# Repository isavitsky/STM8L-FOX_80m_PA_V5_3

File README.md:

# STM8L-FOX_80m_PA_V5_3
STM8L 80m fox power amplifier board schematics and PCB version 5.3

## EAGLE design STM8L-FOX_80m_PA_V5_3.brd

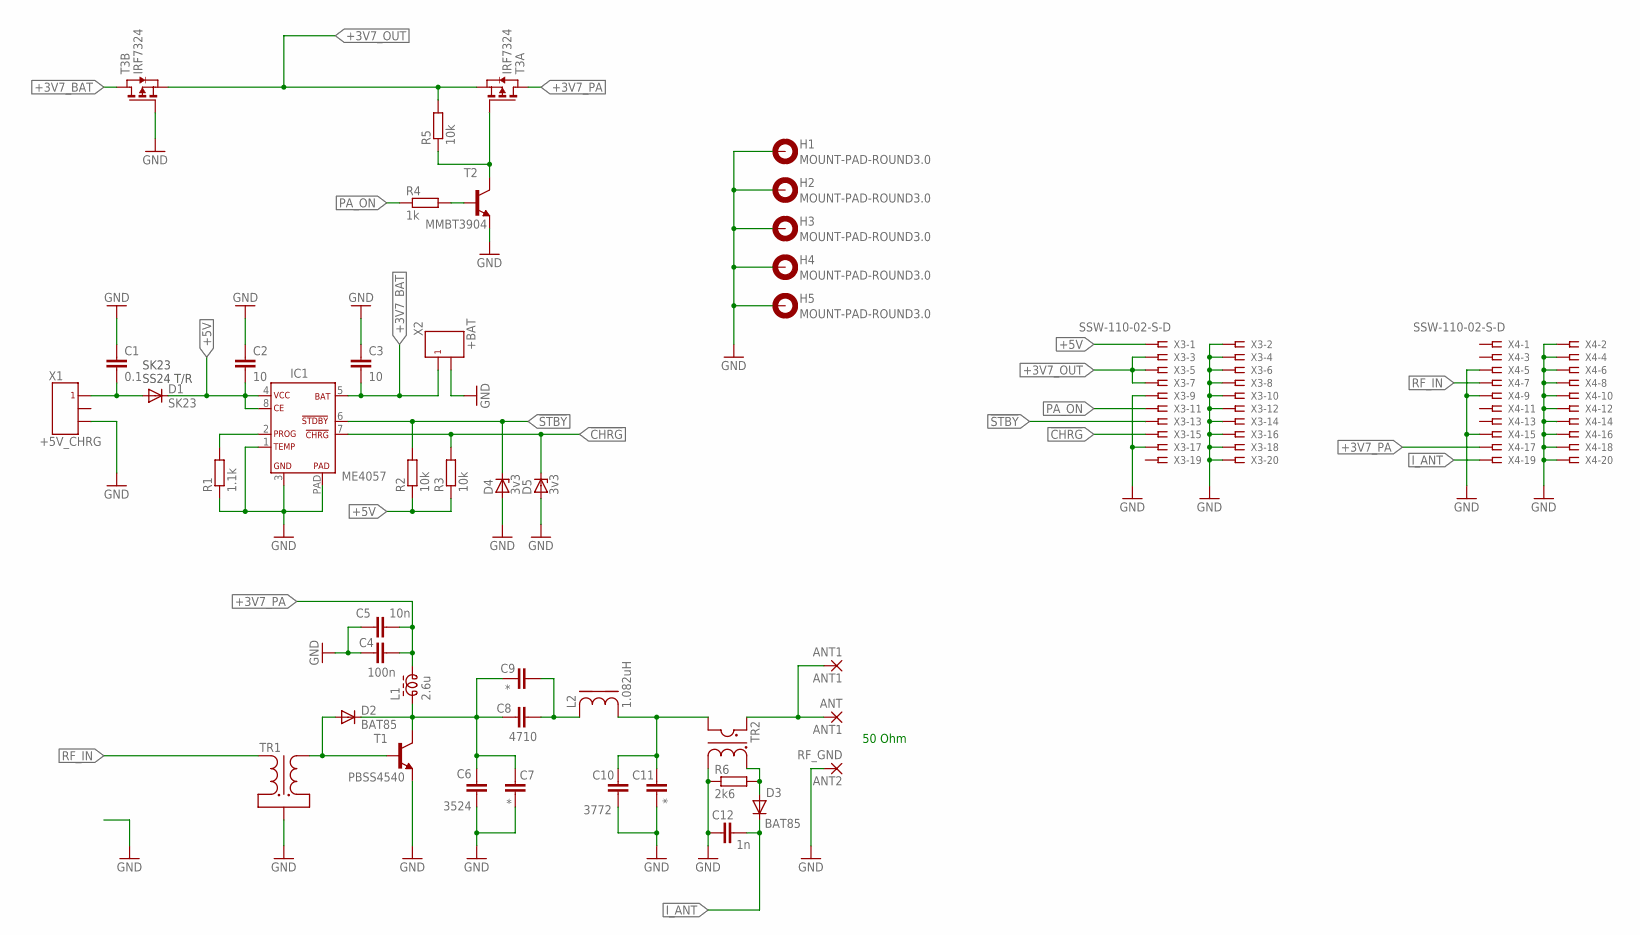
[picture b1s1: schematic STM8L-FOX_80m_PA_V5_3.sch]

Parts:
ANT, ANT1: ANT1; 2,54/0,8
C1: 0.1; C1206K
C2, C3: 10; C1206K
C4: 100n; C1206K
C5: 10n; C1206K
C6: 3524; C1206K
C7, C9, C11: *; C1206K
C8: 4710; C1206K
C10: 3772; C1206K
C12: 1n; C1206K
D1: SK23; DO-214AC
D2, D3: BAT85; DO34-7
D4, D5: 3v3; SOT23
H1, H2, H3, H4, H5: MOUNT-PAD-ROUND3.0; 3,0-PAD
IC1: ME4057A; SOP08-PP
L1: 2.6u; ZD6-3W
L2: 1.082uH; T68_COIL
R1: 1.1k; R1206
R2, R3, R5: 10k; R1206
R4: 1k; R1206
R6: 2k6; R1206
RF_GND: ANT2; 2,54/0,8
T1: PBSS4540; SOT223
T2: MMBT3904; SOT23-BEC
T3: IRF7324; SO8
TR1: K7X4X2_TRANS_1V1
TR2: K7X4X2_TRANS_CURRENT
X1: +5V_CHRG; A2501WR-3P
X2: +BAT; A2501WR-2P
X3, X4: SSW-110-02-S-D

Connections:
!CHRG!: D5.3 (C), IC1.7, R3.2, X3.15
!STBY!: D4.3 (C), IC1.6, R2.2, X3.13
+3V7_BAT: C3.2, IC1.5, T3.5 (D), T3.6 (D), X2.P$1
+3V7_OUT: R5.2, T3.1 (S), T3.3 (S), X3.3, X3.5, X3.7
+3V7_PA: C4.2, C5.1, L1.2, T3.7 (D), T3.8 (D), X4.17
+5V: C2.2, D1.C, IC1.4, IC1.8, R2.1, R3.1, X3.1
CHRGR: C1.2, D1.A, X1.P$1
GND: C1.1, C2.1, C3.1, C4.1, C5.2, C6.2, C7.2, C10.2, C11.2, C12.1, D4.1 (A), D5.1 (A), H1.B3,0, H2.B3,0, H3.B3,0, H4.B3,0, H5.B3,0, IC1.1, IC1.3, IC1.PAD, R1.1, R6.1, RF_GND.1, T1.3 (E), T2.E, T3.4 (G), TR1.P$1, TR2.P$4, X1.P$3, X2.P$2, X3.2, X3.4, X3.6, X3.8, X3.9, X3.10, X3.12, X3.14, X3.16, X3.17, X3.18, X3.20, X4.2, X4.4, X4.5, X4.6, X4.8, X4.9, X4.10, X4.12, X4.14, X4.15, X4.16, X4.18, X4.20
I_ANT: C12.2, D3.C, X4.19
unnamed: R5.1, T2.C, T3.2 (G)
unnamed: C8.2, C9.2, L2.P$1
unnamed: IC1.2, R1.2
unnamed: R4.2, T2.B
unnamed: D2.A, T1.1 (B), TR1.P$3
unnamed: C6.1, C7.1, C8.1, C9.1, D2.C, L1.1, T1.2 (C), T1.4 (C)
unnamed: C10.1, C11.1, L2.P$2, TR2.P$2
unnamed: ANT.1, ANT1.1, TR2.P$1
unnamed: D3.A, R6.2, TR2.P$3
PA_ON: R4.1, X3.11
RF_IN: TR1.P$2, X4.7

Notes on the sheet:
SK23 SS24 T/R
50 Ohm

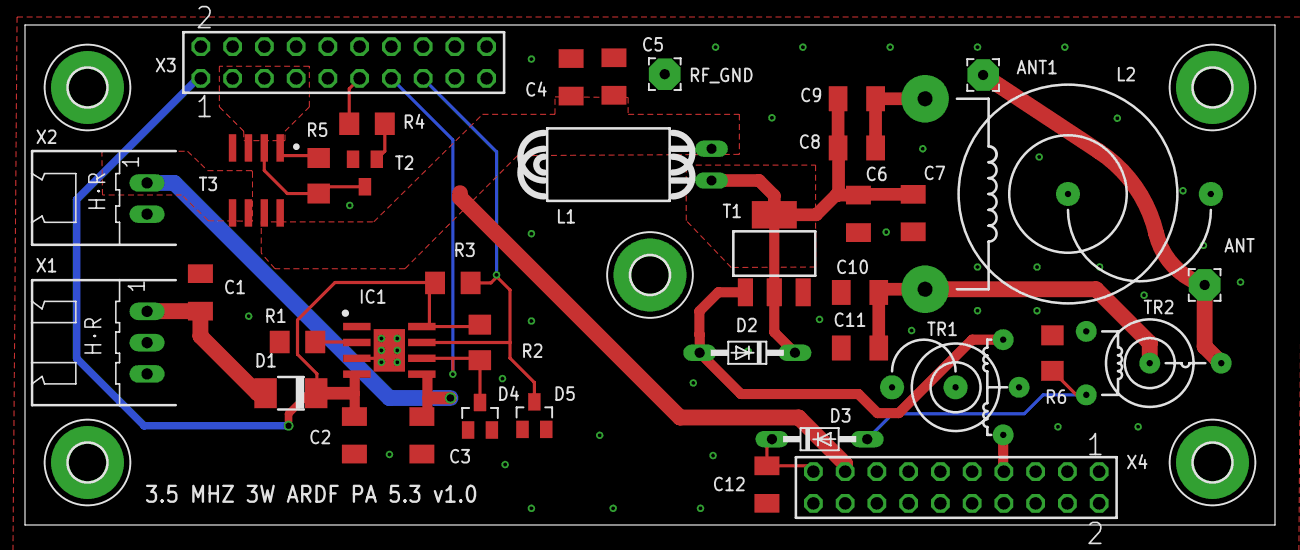
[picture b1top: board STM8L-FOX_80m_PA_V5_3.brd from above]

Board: 2 copper layers, 100.0 x 40.0 mm, 43 parts (0 on the bottom side), 20 nets.
